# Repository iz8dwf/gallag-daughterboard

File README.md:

# gallag-daughterboard
Arcade "gallag blue" Galaga bootleg daughterboard substitute

More information here:
https://www.youtube.com/watch?v=VK13G8KH0y8

If you're going to build this project, please contact me, I would like
to experiment with a new CPLD code that eliminates the need for the wire
connected to the main pcb. (Yes, no time to build another, so I need beta
testers).

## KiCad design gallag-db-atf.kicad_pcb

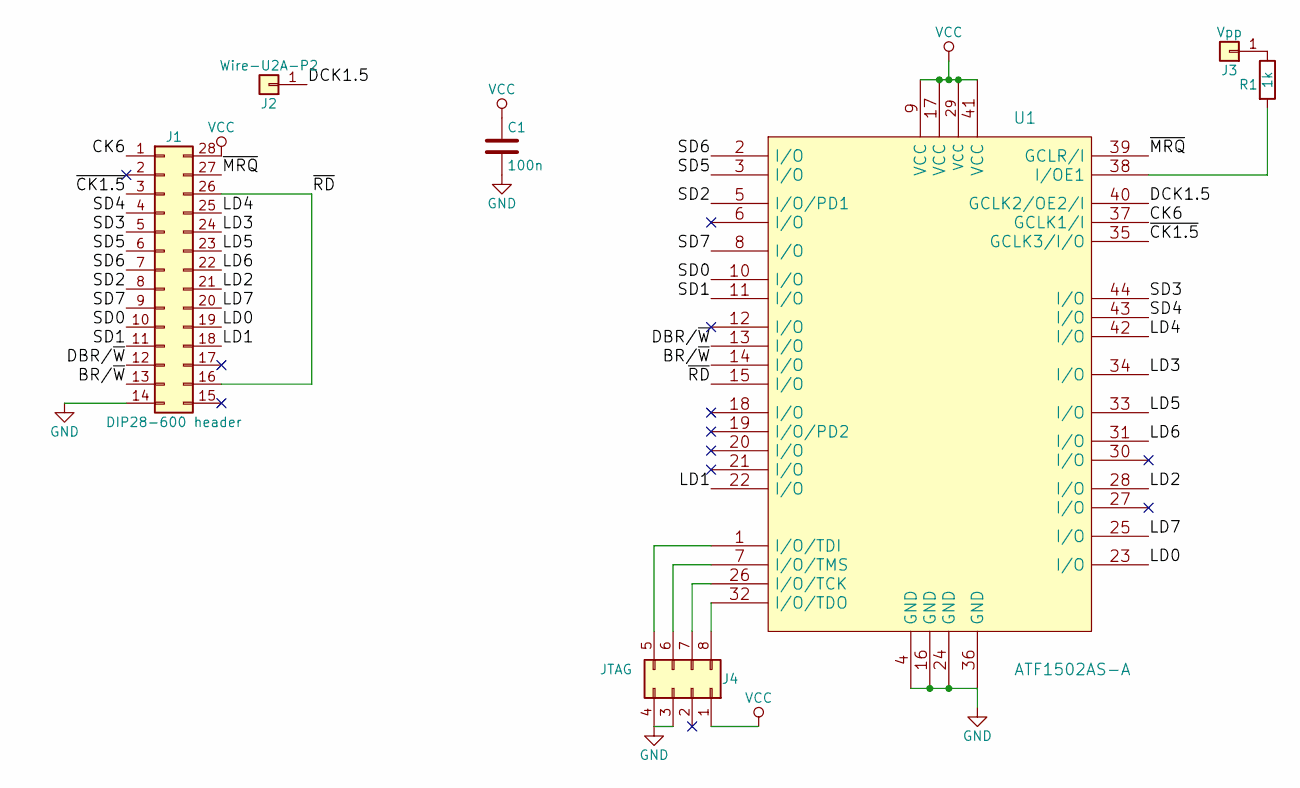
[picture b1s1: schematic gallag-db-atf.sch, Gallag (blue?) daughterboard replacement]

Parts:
C1: 100n; C_0805_HandSoldering
J1: DIP28-600 header; DIP-28_W15.24mm
J2: Wire-U2A-P2; Test_Point_THTPad_1.5x1.5mm_Drill0.7mm
J3: Vpp; Test_Point_Pad_d1.0mm
J4: JTAG; Pin_Header_Straight_2x04_Pitch2.54mm
R1: 1k; R_0805_HandSoldering
U1: ATF1502AS-A; TQFP-44_10x10mm_Pitch0.8mm

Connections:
/BR/~W: J1.13, U1.14 (I/O)
/CK6: J1.1, U1.37 (GCLK1/I)
/DBR/~W: J1.12, U1.13 (I/O)
/DCK1.5: J2.1, U1.40 (GCLK2/OE2/I)
/LD0: J1.19, U1.23 (I/O)
/LD1: J1.18, U1.22 (I/O)
/LD2: J1.21, U1.28 (I/O)
/LD3: J1.24, U1.34 (I/O)
/LD4: J1.25, U1.42 (I/O)
/LD5: J1.23, U1.33 (I/O)
/LD6: J1.22, U1.31 (I/O)
/LD7: J1.20, U1.25 (I/O)
/SD0: J1.10, U1.10 (I/O)
/SD1: J1.11, U1.11 (I/O)
/SD2: J1.8, U1.5 (I/O/PD1)
/SD3: J1.5, U1.44 (I/O)
/SD4: J1.4, U1.43 (I/O)
/SD5: J1.6, U1.3 (I/O)
/SD6: J1.7, U1.2 (I/O)
/SD7: J1.9, U1.8 (I/O)
/~CK1.5: J1.3, U1.35 (GCLK3/I/O)
/~MRQ: J1.27, U1.39 (GCLR/I)
/~RD: J1.16, J1.26, U1.15 (I/O)
GND: C1.2, J1.14, J4.3, J4.4, U1.4 (GND), U1.16 (GND), U1.24 (GND), U1.36 (GND)
unnamed: J3.1, R1.1
unnamed: J4.5, U1.1 (I/O/TDI)
unnamed: J4.6, U1.7 (I/O/TMS)
unnamed: J4.7, U1.26 (I/O/TCK)
unnamed: J4.8, U1.32 (I/O/TDO)
unnamed: R1.2, U1.38 (I/OE1)
VCC: C1.1, J1.28, J4.1, U1.9 (VCC), U1.17 (VCC), U1.29 (VCC), U1.41 (VCC)

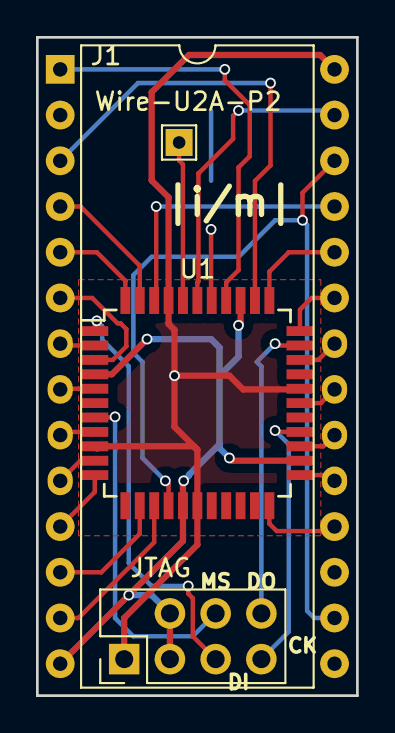
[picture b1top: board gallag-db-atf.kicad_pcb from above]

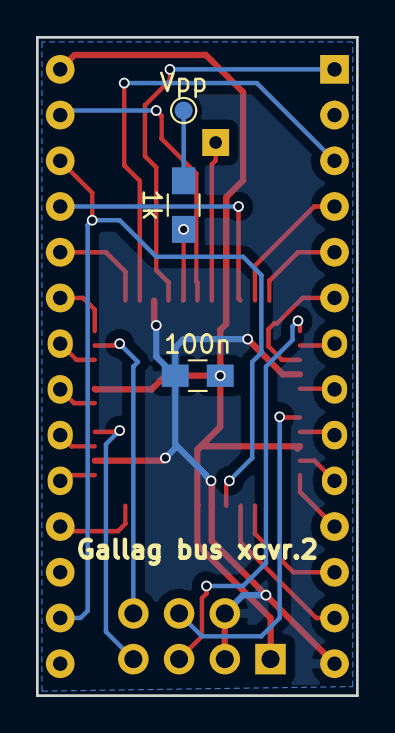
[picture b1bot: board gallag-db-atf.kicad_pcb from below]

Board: 2 copper layers, 17.8 x 36.6 mm, 7 parts (3 on the bottom side), 31 nets.

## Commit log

2023-11-25 first import
2023-11-25 new readme
2025-06-14 removed unnecessary file
